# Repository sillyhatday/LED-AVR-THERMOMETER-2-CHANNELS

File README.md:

# 2 Channel Temperature Monitor

## 📢 Introduction

This came about as a break from the [nixie clock](https://github.com/sillyhatday/IN-12-NIXIE-CLOCK) project that was taking a long time to progress.

It is a 2 channel temperature monitor that is intended for inside and outside temperature monitoring.

>[!NOTE]
>While this project is functional, the code is a mess. It requires a rewrite.

---

## 🔨 Hardware

| Part Description | Part Number | Package | Quantity |
| --------------------- | ------------------ | ----------- | ----------- |
| Microcontroller | ATmega8A | DIP-28 | 1 |
| 4x 7 Segment Display | SR420561N | ?? | 1 |
| Voltage Reference | TL431 | TO-92-3 | 1 |
| Temperature Sensor | MCP9700 | TO-92 | 1 |
| Resistors | 470R | L6.3xD2.5xP10.16 | 8 |
| Resistors | 1K | L6.3xD2.5xP10.16 | 1 |
| Resistors | 10K | L6.3xD2.5xP10.16 | 7 |
| Capacitors | 20pF | D3.4xW2.1xP2.5 | 2 |
| Capacitors | 100nF | D3.0xW2.0xP2.5 | 3 |
| Capacitors | 1uF | ?? | 2 |
| Capacitors | 10uF | ?? | 1 |
| Buttons | PS-7054DVB-6PN | ?? | 2 |

---

## 📔 Functional Description

* The sensors used for temperature sensing are two MCP9700 packages. These are easy to use, not requiring external circuit conditioning. These can do negative temperatures without needing negative voltages, using a 500mV offset for 0c.

* For an air temperature monitor, the range does not need to be extreme. For the temperatures expected in Europe, -20c to 50c would be more than enough. For the most part things are between -3c and 35c. The range available for this project is -50c to 154.6c. A span of 204.6c.

* An accurate voltage refernce is needed to compare the sensor voltage with. For this the TL431 is used, it is another easy to use soloution. It has an output of 2.495v. For easy maths (and a large shortcut), having a reference voltage a multiple of the maximum ADC bits makes things simple. The 10-bit ADC is 0 - 1023. Setting the refrence voltage to 2.048v, through the use of a voltage divider network, is close enough to double.

* You may see that the finest change of temperature is 0.2c. That is 2048mV / 1023ADC = 2mV. The MCP9700 sensor output changes 10mV / 1c. As this setup requires 2mV per 1 ADC, 10mV / 2mV = 5. Finally, 5 ADC changes per 1c means, 1c / 5 = 0.2c. Should there not be a nice relation between voltage and ADC, the maths become more involved. Along the lines of: ADC reading > convert ADC to voltage > convert voltage to temperature. This can involve the use of floating point numbers. When getting to oversamlping, this complicates things further.

* The device has a single screen displaying temperature. It has two buttons. One for selecting which sensor is being displayed and the other to cycle through peak readings. These being: indoor high, indoor low, outdoor high & outdoor low. Peak readings are always being updated regardless of what is actively displayed on screen. These values can be reset by shorting the jumper connections on the back of the board. This can also be connected to a button if desired.

* I ended up using a mini 3 pin XLR connector for the outdoor temperature sensor, with the idea of it being removable should I wish to not use it, or I need to disconnect my outdoor sensor that isn't easily movable. I had the indoor sensor inside the case, the thought being it would help filter out any air current that could cause wild temperature reading changes. This did not work as the heat from the MCU was enough to ruin the accuracy. For accurate readings, the sensor should also be on a wire and positioned in the rood so that it is away from strong air currents. There is software averaging to reduce wild display changes.

>[!NOTE]
>The project code is honestly a mess. It's currently half rewritten in a better way using state machines. For now, this works well enough.

>[!TIP]
>Direct sunlight will heat up the outdoor sensor. A screen is required to help reduce this effect.

## ⚫ Progress

### 🟢 Done
- Build a functional temperature monitor that can read two channels
- Implement peak temperature readings and store them into EEPROM
- Add EEPROM check for knowing if to initialise memory space.
- Display text on screen when interacting with the button functions.

### 🟡 Working On
- Rewriting the whole code to use a traditional state machine based structure.
- Removing known bugs.

### ⚪ Next
- Nothing. A whole new project expanding on this one.

### 🔴 Known Bugs
- Temperatures over 100c corrupt adjacent memory space. Needs memory allocations moving.
- Flickering display when using the button functions. Race conditions, the rewrite will fix.
  
---

## Photos

### PCB Render

### Final Concept

### Current Build

---

## Tools

- Tools: Arduino IDE 1.8.19 – MiniCore for ATMEGA8

---

## Links

🛍️ Inside Gadgets Shop: https://shop.insidegadgets.com <br>
📎 Inside Gadgets GitHub: https://github.com/insidegadgets <br>
📷 Inside Gadgets Insta: https://www.instagram.com/inside.gadgets <br>
🖇️ Bytendo Mods GitHub: https://github.com/bytendomods <br>
🐭 Bucket Mouse: https://github.com/Bucket-Mouse <br>
🛒 Natalie Shop: https://nataliethenerd.com/ <br>
🤓 Natalie GitHub: https://github.com/natalie-lang/natalie <br>
💡 Danyk Project 1: https://danyk.cz/avr_tep2_en.html <br>
🌡️ Danyk Project 2: https://danyk.cz/avr_tep_en.html <br>

---

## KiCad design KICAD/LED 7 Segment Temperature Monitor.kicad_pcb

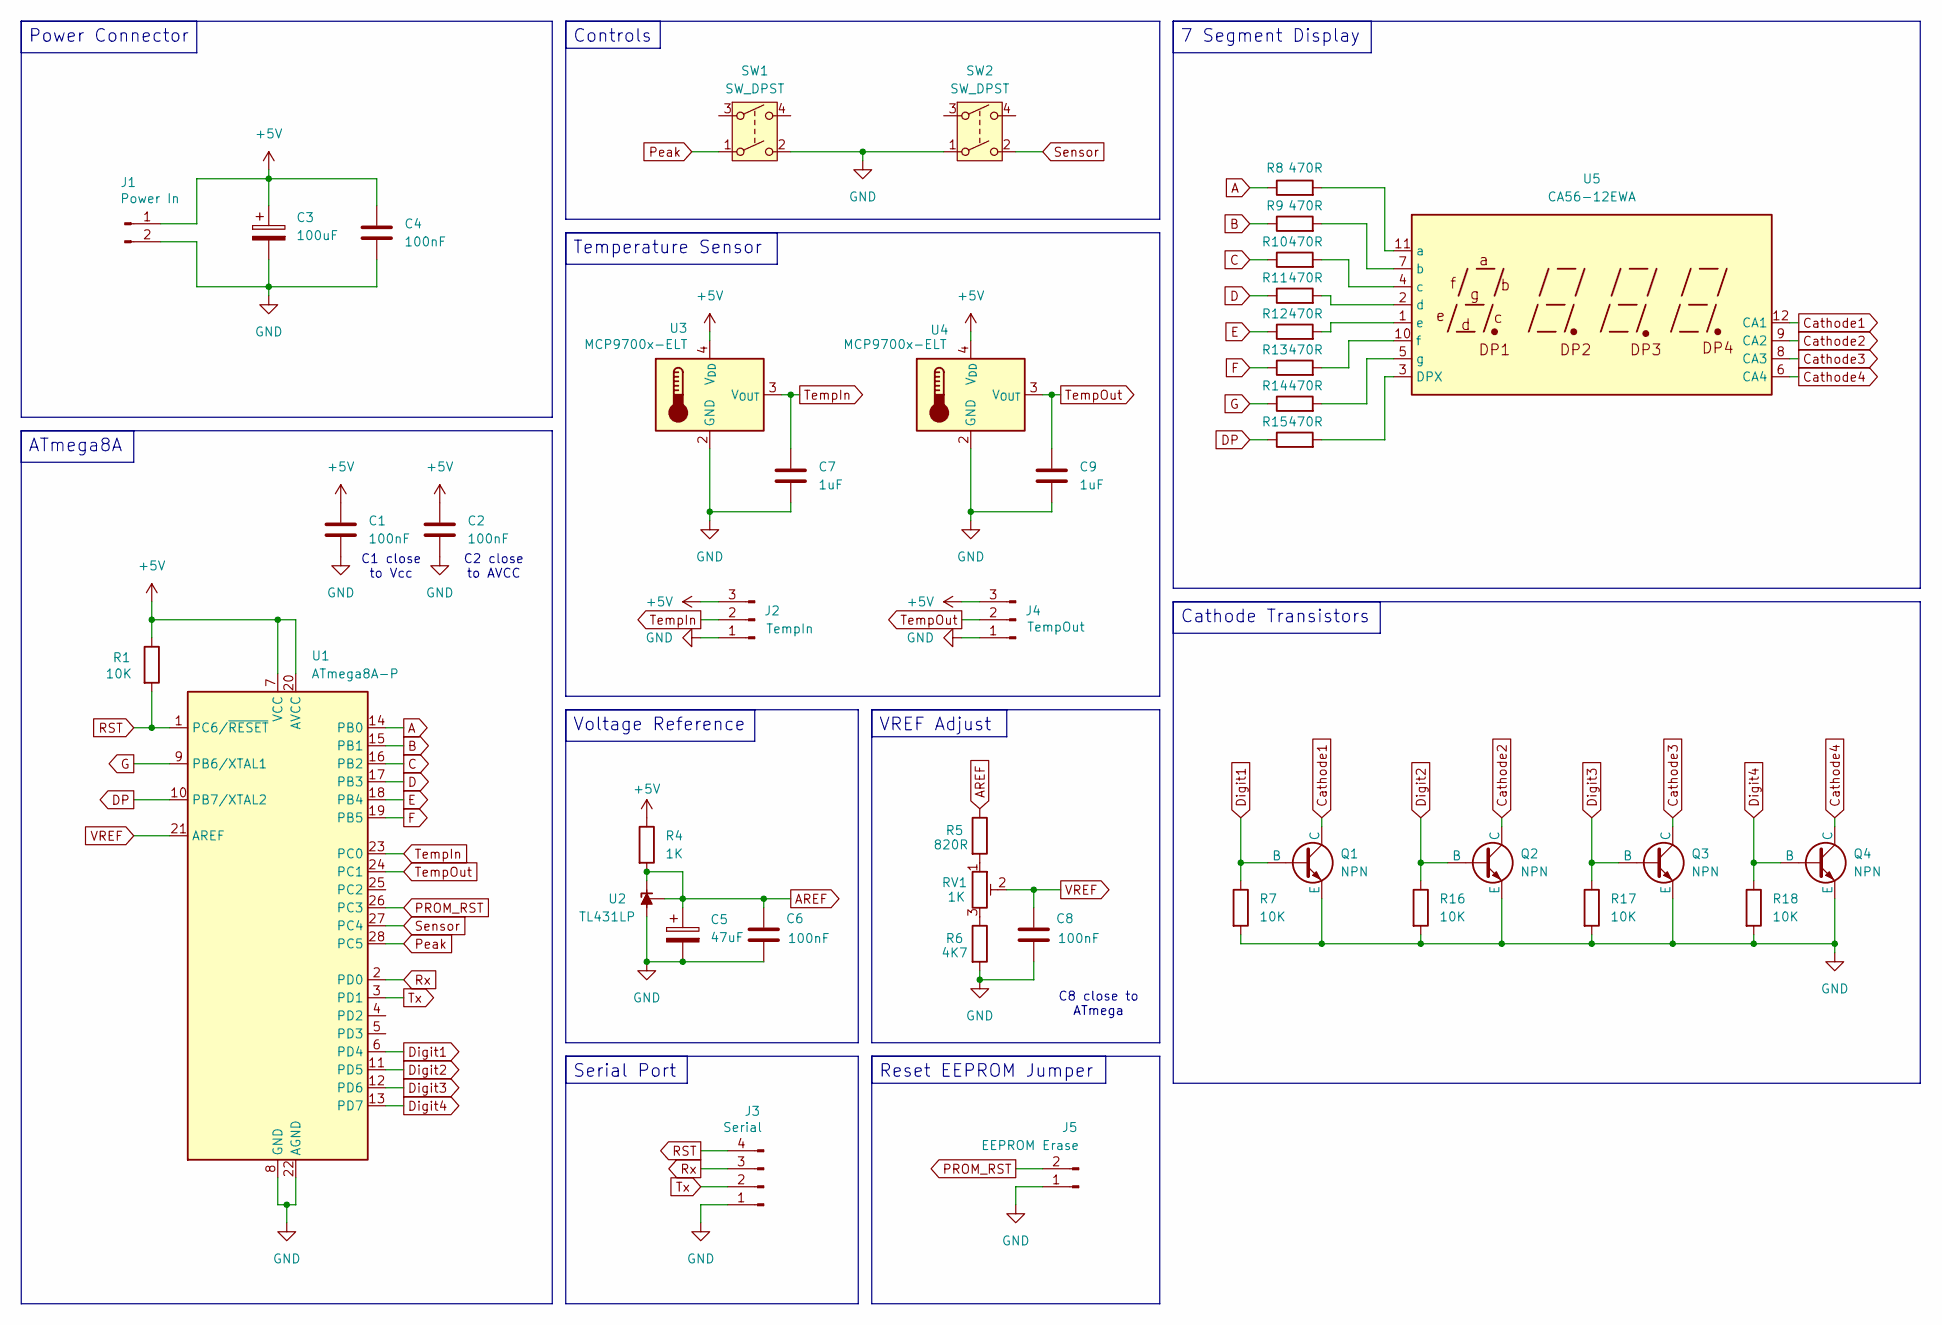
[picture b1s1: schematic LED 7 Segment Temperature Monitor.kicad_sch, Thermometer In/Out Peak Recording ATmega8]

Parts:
C1, C2, C4, C6, C8: 100nF; C_Disc_D5.0mm_W2.5mm_P2.50mm
C3: 100uF; CP_Radial_D5.0mm_P2.50mm
C5: 47uF; CP_Radial_D5.0mm_P2.50mm
C7, C9: 1uF; C_Disc_D5.0mm_W2.5mm_P2.50mm
J1: Power In; PinHeader_1x02_P2.54mm_Vertical
J2: TempIn; PinHeader_1x03_P2.54mm_Vertical
J3: Serial; PinHeader_1x04_P2.54mm_Vertical
J4: TempOut; PinHeader_1x03_P2.54mm_Vertical
J5: EEPROM Erase; PinHeader_1x02_P2.54mm_Vertical
Q1, Q2, Q3, Q4: NPN; TO-92_Inline
R1, R7, R16, R17, R18: 10K; R_Axial_DIN0207_L6.3mm_D2.5mm_P10.16mm_Horizontal
R4: 1K; R_Axial_DIN0207_L6.3mm_D2.5mm_P10.16mm_Horizontal
R5: 820R; R_Axial_DIN0207_L6.3mm_D2.5mm_P10.16mm_Horizontal
R6: 4K7; R_Axial_DIN0207_L6.3mm_D2.5mm_P10.16mm_Horizontal
R8, R9, R10, R11, R12, R13, R14, R15: 470R; R_Axial_DIN0207_L6.3mm_D2.5mm_P10.16mm_Horizontal
RV1: 1K; Potentiometer_Bourns_3386C_Horizontal
SW1, SW2: SW_DPST; SHOU HAN 5.8 WSPT
U1: ATmega8A-P; DIP-28_W7.62mm_Socket
U2: TL431LP; TO-92_Inline
U3, U4: MCP9700x-ELT
U5: CA56-12EWA

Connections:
+5V: C1.1, C2.1, C3.1, C4.1, J1.1, J2.3, J4.3, R1.1, R4.1, U1.7 (VCC), U1.20 (AVCC), U3.4 (V_{DD}), U4.4 (V_{DD})
A: R8.1, U1.14 (PB0)
AREF: C5.1, C6.1, R4.2, R5.1, U2.1 (REF), U2.3 (K)
B: R9.1, U1.15 (PB1)
C: R10.1, U1.16 (PB2)
Cathode1: Q1.1 (C), U5.12 (CA1)
Cathode2: Q2.1 (C), U5.9 (CA2)
Cathode3: Q3.1 (C), U5.8 (CA3)
Cathode4: Q4.1 (C), U5.6 (CA4)
D: R11.1, U1.17 (PB3)
DP: R15.1, U1.10 (PB7/XTAL2)
Digit1: Q1.2 (B), R7.1, U1.6 (PD4)
Digit2: Q2.2 (B), R16.1, U1.11 (PD5)
Digit3: Q3.2 (B), R17.1, U1.12 (PD6)
Digit4: Q4.2 (B), R18.1, U1.13 (PD7)
E: R12.1, U1.18 (PB4)
F: R13.1, U1.19 (PB5)
G: R14.1, U1.9 (PB6/XTAL1)
GND: C1.2, C2.2, C3.2, C4.2, C5.2, C6.2, C7.2, C8.2, C9.2, J1.2, J2.1, J3.1, J4.1, J5.1, Q1.3 (E), Q2.3 (E), Q3.3 (E), Q4.3 (E), R6.2, R7.2, R16.2, R17.2, R18.2, SW1.2, SW2.1, U1.8 (GND), U1.22 (AGND), U2.2 (A), U3.2 (GND), U4.2 (GND)
unnamed: R5.2, RV1.1
unnamed: R6.1, RV1.3
unnamed: R15.2, U5.3 (DPX)
unnamed: R8.2, U5.11 (a)
unnamed: R9.2, U5.7 (b)
unnamed: R10.2, U5.4 (c)
unnamed: R11.2, U5.2 (d)
unnamed: R12.2, U5.1 (e)
unnamed: R13.2, U5.10 (f)
unnamed: R14.2, U5.5 (g)
PROM_RST: J5.2, U1.26 (PC3)
Peak: SW1.1, U1.28 (PC5)
RST: J3.4, R1.2, U1.1 (PC6/~RESET)
Rx: J3.3, U1.2 (PD0)
Sensor: SW2.2, U1.27 (PC4)
TempIn: C7.1, J2.2, U1.23 (PC0), U3.3 (V_{OUT})
TempOut: C9.1, J4.2, U1.24 (PC1), U4.3 (V_{OUT})
Tx: J3.2, U1.3 (PD1)
VREF: C8.1, RV1.2, U1.21 (AREF)

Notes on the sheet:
C2 close to AVCC
C1 close to Vcc
C8 close to ATmega
7 Segment Display
Power Connector
ATmega8A
Controls
Voltage Reference
Reset EEPROM Jumper
Temperature Sensor
Cathode Transistors
Serial Port
VREF Adjust

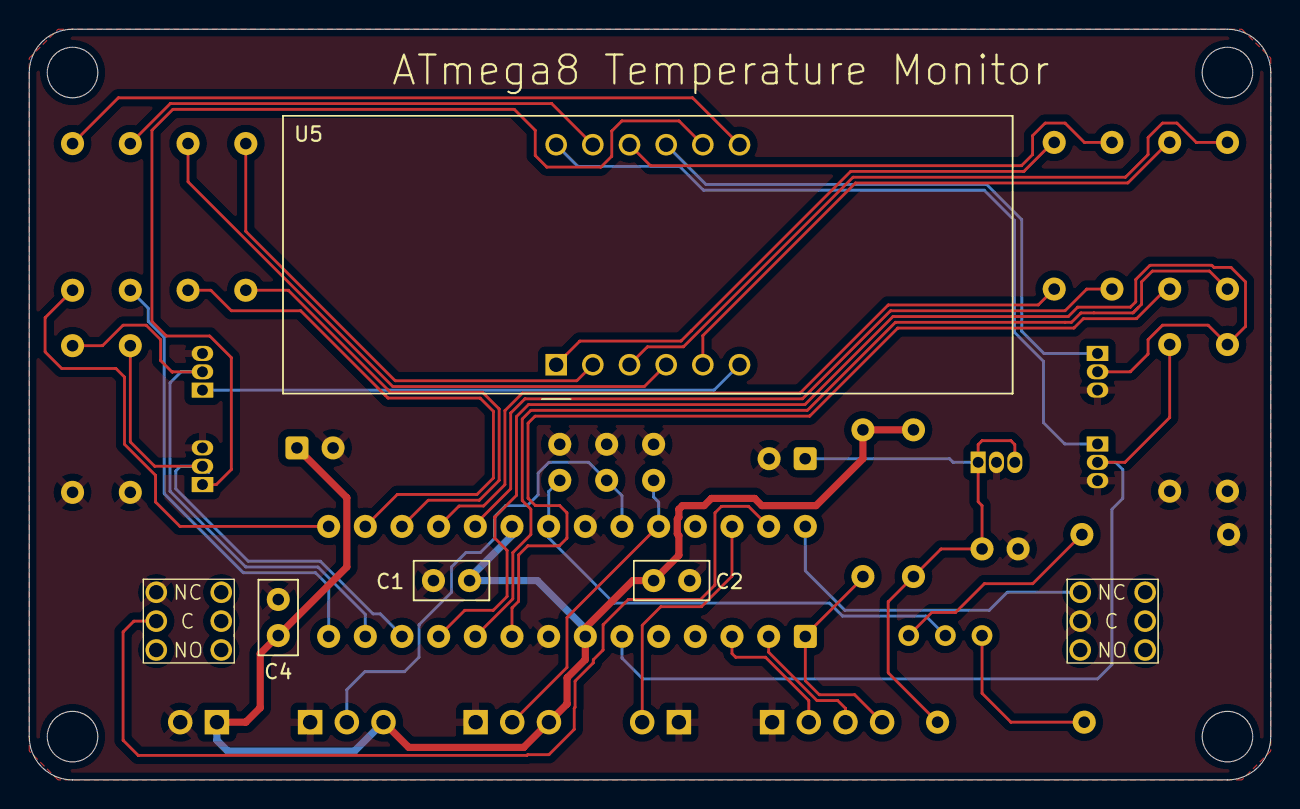
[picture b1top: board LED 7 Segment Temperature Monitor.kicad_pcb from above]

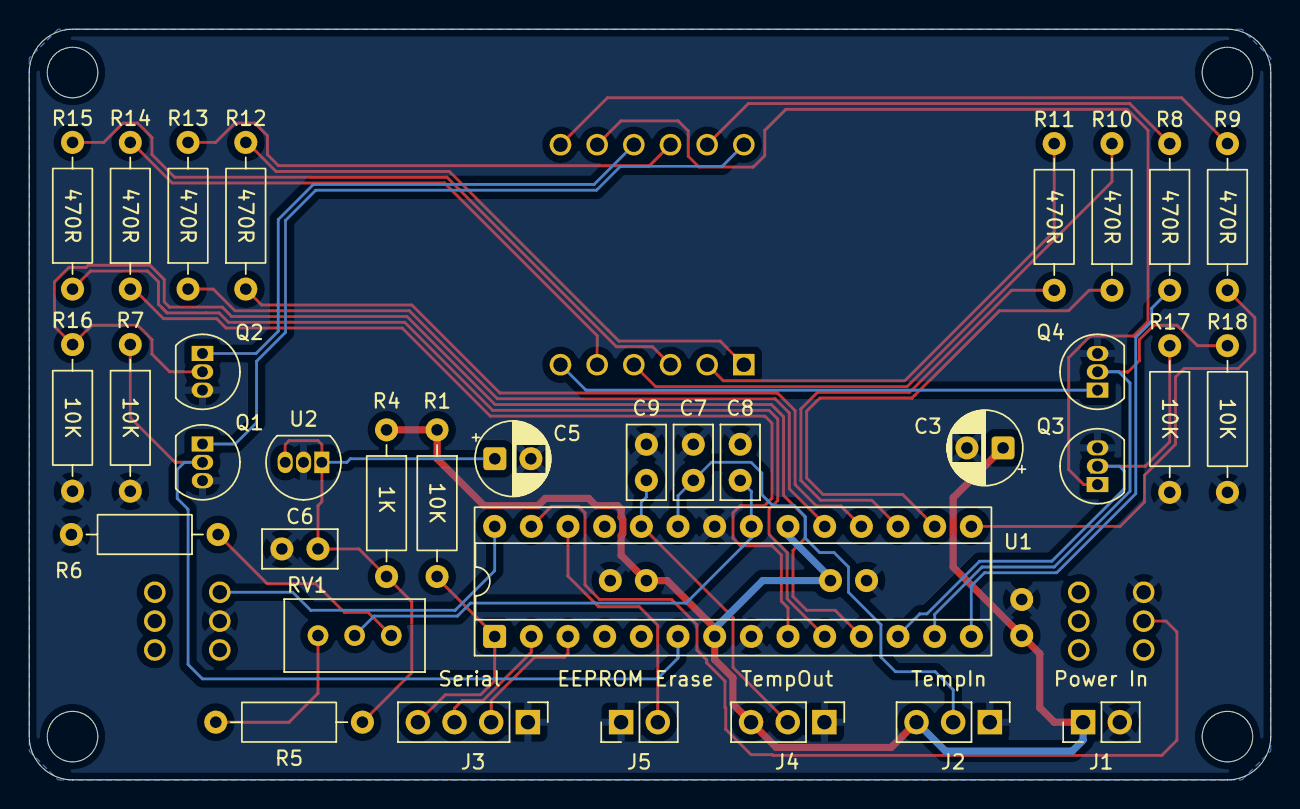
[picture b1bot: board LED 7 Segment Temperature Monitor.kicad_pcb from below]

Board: 2 copper layers, 86.0 x 52.0 mm, 40 parts (34 on the bottom side), 38 nets.

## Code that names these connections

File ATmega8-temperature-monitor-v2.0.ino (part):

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
// Todo List:
// Use internal clock, not external to clear port B pins (DONE)
// Move all anode output pins to port B. Pins 14, 15, 16, 17, 18, 19, 9 & 10. PB0 - 7 (DONE)
// Move all cathode pins to port D. Pins 4, 5, 6, 11, 12, 13. PD2 - 7 (Already done)
// Sort out EEPROM data overflow. Max temp is 3 digits not 2.
// Change ADC sampling rate to counter based on ISR not time.
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
// **************************************** Button Constants ********************************************** //

const byte INDOOR_SENSOR =                           A0;                         // Sensor inside input pin
const byte OUTDOOR_SENSOR =                          A1;                         // Sensor outside input pin
const byte SELECT =                                  A4;                         // Sensor select button
const byte PEAK =                                    A5;                         // Peak value display
const byte RESET =                                   A3;                         // Clear EEPROM jumper
const byte DEBOUNCE_DELAY =                         250;                         // Button debounce millis

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const byte EEPROM_ADDRESS_IN_LOW =                    3;                         // Indoor temp low
const byte EEPROM_ADDRESS_OUT_HIGH =                  5;                         // Outdoor temp high
const byte EEPROM_ADDRESS_OUT_LOW =                   7;                         // Outdoor temp low
const byte EEPROM_ADDRESS_IN_OR_OUT =                 9;                         // Last sensor displayed
const byte EEPROM_DATA_SIGNITURE =                 0x55;                         // EEPROM initialised data
const int EEPROM_DELAY =                           6000;                         // millis to prevent garbage on boot

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
const byte NUM_DISPLAYS =                             4;
const byte NUM_SEGMENTS =                             7;
const uint16_t DISPLAY_TIME =                      2000;                         // Time to show which sensor is selected
const uint16_t DISPLAY_TIME_SHORT =                1000;

// **************************************** Sensor Constants ********************************************** //

const byte AVERAGE_SAMPLE_TIME =                      5;                         // heartBeat count (20s)
const int SAMPLE_INTERVAL =                        4000;                         // Sample frequency ms
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
// **************************************** Display Variables ************************************************ //

uint16_t peakDataValue =                              0;                         // Peak value to show
uint8_t digits[4] =                        {0, 0, 0, 0};                         // Main display buffer
uint8_t live[4] =                          {0, 0, 0, 0};                         // Live temperature reading
uint8_t text[4] =                          {0, 0, 0, 0};                         // Text buffer
uint8_t peak[4] =                          {0, 0, 0, 0};                         // Peak value buffer
uint8_t currentDigit =                                0;                         // Active digit on display now
uint32_t showTextStart =                              0;                         // Time when showing sensor info started
uint32_t showValuesStart =                            0;

// **************************************** Sensor Variables ************************************************* //

int16_t signedIndoorTemperature =                     0;                         // Indoor temperature celcius x10
int16_t signedOutdoorTemperature =                    0;                         // Outdoor temperature celcius x10
volatile uint16_t heartBeat =                         0;                         // Sensor sample freq

// ***************************************** Button Variables ********************************************* //

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// ***************************************** Global Variables ********************************************* //

uint32_t previousMicros =                                  0;                         // Last update time of display micros
uint32_t previousMillis =                                  0;                         // Last update time of sensor reading
uint16_t rollingAverageIndoor[8] =  {0, 0, 0, 0, 0, 0, 0, 0};                         // Average for stability
uint16_t rollingAverageOutdoor[8] = {0, 0, 0, 0, 0, 0, 0, 0};                         // Average for stability
uint16_t rollingAverageIndoorValue =                       0;
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// ADC Reference
  analogReference(EXTERNAL);

// PORTB Setup - Anodes            -     Arduino Pin -> 8, 9, 10, 11, 12, 13, PB6, PB7  -  Port Pin: PB7...0
  DDRB = 0b11111111;
  PORTB = 0b00000000;

// PORTC Setup - Sensors/Buttons   -     Arduino Pin -> A0, A1, A3, A4, A5  -  Port Pin: PC0, PC1, PC3, PC4, PC5
  DDRC = 0b00000000;
  PORTC = 0b00111100;

// PORTD Setup - Cathodes          -     Arduino Pin -> 7, 6, 5, 4   -   Port Pin: PD7...4
  DDRD = 0b11110000;
  PORTD = 0b00001111;

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
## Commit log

2025-12-10 Update README.md
    Started parts table
2025-12-11 Update README.md
    Updated parts list
2026-06-02 Update README.md
    Full rewrite
2026-06-02 Add files via upload
    Added final first version & in progress second version
2026-06-02 Create LICENSE
2026-06-04 Update README.md
    Added renders
2026-06-04 Create dummy
2026-06-04 Add files via upload
    Large renders
2026-06-04 Add files via upload
    step files uploaded
2026-06-25 Update README.md
    Updated readme
2026-06-25 Create wer da files?
2026-06-28 Update README.md
    images
